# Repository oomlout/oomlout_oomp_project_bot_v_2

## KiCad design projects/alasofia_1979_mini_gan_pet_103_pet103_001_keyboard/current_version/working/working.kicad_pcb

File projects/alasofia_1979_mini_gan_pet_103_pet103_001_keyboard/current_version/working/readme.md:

# 1979_mini_gan_pet_103
 
## summary 
* id: alasofia_1979_mini_gan_pet_103_pet103_001_keyboard
* user: alasofia
* name: 1979_mini_gan_pet_103
* board: pet103_001_keyboard
* repo: https://github.com/Alasofia/1979-MINI-GAN-PET-103
* src_file_repo_kicad_pcb: KiCad/PET103_001_Keyboard/PET103_001_Keyboard.kicad_pcb
* src_file_repo_kicad_pcb_link: https://github.com/Alasofia/1979-MINI-GAN-PET-103/tree/main/KiCad/PET103_001_Keyboard/PET103_001_Keyboard.kicad_pcb

* src_file_repo_sch: KiCad/PET103_001_Keyboard/PET103_001_Keyboard.sch
* src_file_repo_sch_link: https://github.com/Alasofia/1979-MINI-GAN-PET-103/tree/main/KiCad/PET103_001_Keyboard/PET103_001_Keyboard.sch
* full details link: https://github.com/oomlout/oomlout_oomp_project_bot_v_2/tree/main/projects/alasofia_1979_mini_gan_pet_103_pet103_001_keyboard/current_version/working  

## schematic  
  
[schematic (pdf)](working_schematic.pdf) 

## pcb  

[board (pdf)](working.pdf)  

## working_bom
| Id | Designator | Footprint | Quantity | Designation | Supplier and ref |  | None | 
| --- | --- | --- | --- | --- | --- | --- | --- | 
| 1 | R1 | R_Axial_DIN0207_L6.3mm_D2.5mm_P10.16mm_Horizontal | 1 | 5K |  |  | [''] | 
| 2 | R2,R3 | R_Axial_DIN0207_L6.3mm_D2.5mm_P10.16mm_Horizontal | 2 | 4K6 |  |  | [''] | 
| 3 | R4,R5 | R_Axial_DIN0207_L6.3mm_D2.5mm_P10.16mm_Horizontal | 2 | 4K |  |  | [''] | 
| 4 | R6,R7 | R_Axial_DIN0207_L6.3mm_D2.5mm_P10.16mm_Horizontal | 2 | 3K5 |  |  | [''] | 
| 5 | R8,R9 | R_Axial_DIN0207_L6.3mm_D2.5mm_P10.16mm_Horizontal | 2 | 3K2 |  |  | [''] | 
| 6 | R10 | R_Axial_DIN0207_L6.3mm_D2.5mm_P10.16mm_Horizontal | 1 | 3K |  |  | [''] | 
| 7 | R11 | R_Axial_DIN0207_L6.3mm_D2.5mm_P10.16mm_Horizontal | 1 | 2K8 |  |  | [''] | 
| 8 | R12 | R_Axial_DIN0207_L6.3mm_D2.5mm_P10.16mm_Horizontal | 1 | 2K6 |  |  | [''] | 
| 9 | R13,R14 | R_Axial_DIN0207_L6.3mm_D2.5mm_P10.16mm_Horizontal | 2 | 2K5 |  |  | [''] | 
| 10 | R15 | R_Axial_DIN0207_L6.3mm_D2.5mm_P10.16mm_Horizontal | 1 | 2K3 |  |  | [''] | 
| 11 | R16,R17 | R_Axial_DIN0207_L6.3mm_D2.5mm_P10.16mm_Horizontal | 2 | 2K |  |  | [''] | 
| 12 | R18 | R_Axial_DIN0207_L6.3mm_D2.5mm_P10.16mm_Horizontal | 1 | 1K9 |  |  | [''] | 
| 13 | R19 | R_Axial_DIN0207_L6.3mm_D2.5mm_P10.16mm_Horizontal | 1 | 1K8 |  |  | [''] | 
| 14 | R20 | R_Axial_DIN0207_L6.3mm_D2.5mm_P10.16mm_Horizontal | 1 | 1K7 |  |  | [''] | 
| 15 | R21 | R_Axial_DIN0207_L6.3mm_D2.5mm_P10.16mm_Horizontal | 1 | 1K5 |  |  | [''] | 
| 16 | R22,R23 | R_Axial_DIN0207_L6.3mm_D2.5mm_P10.16mm_Horizontal | 2 | 1K4 |  |  | [''] | 
| 17 | R24 | R_Axial_DIN0207_L6.3mm_D2.5mm_P10.16mm_Horizontal | 1 | 1K3 |  |  | [''] | 
| 18 | R25 | R_Axial_DIN0207_L6.3mm_D2.5mm_P10.16mm_Horizontal | 1 | 22K |  |  | [''] | 

## bom_schematic
| Ref | Qnty | Value | Cmp name | Footprint | Description | Vendor | DNP | 
| --- | --- | --- | --- | --- | --- | --- | --- | 
| R1 | 1 | 5K | R_Small_US | Resistor_THT:R_Axial_DIN0207_L6.3mm_D2.5mm_P10.16mm_Horizontal | Resistor, small US symbol |  |  | 
| R2, R3 | 2 | 4K6 | R_Small_US | Resistor_THT:R_Axial_DIN0207_L6.3mm_D2.5mm_P10.16mm_Horizontal | Resistor, small US symbol |  |  | 
| R4, R5 | 2 | 4K | R_Small_US | Resistor_THT:R_Axial_DIN0207_L6.3mm_D2.5mm_P10.16mm_Horizontal | Resistor, small US symbol |  |  | 
| R6, R7 | 2 | 3K5 | R_Small_US | Resistor_THT:R_Axial_DIN0207_L6.3mm_D2.5mm_P10.16mm_Horizontal | Resistor, small US symbol |  |  | 
| R8, R9 | 2 | 3K2 | R_Small_US | Resistor_THT:R_Axial_DIN0207_L6.3mm_D2.5mm_P10.16mm_Horizontal | Resistor, small US symbol |  |  | 
| R10 | 1 | 3K | R_Small_US | Resistor_THT:R_Axial_DIN0207_L6.3mm_D2.5mm_P10.16mm_Horizontal | Resistor, small US symbol |  |  | 
| R11 | 1 | 2K8 | R_Small_US | Resistor_THT:R_Axial_DIN0207_L6.3mm_D2.5mm_P10.16mm_Horizontal | Resistor, small US symbol |  |  | 
| R12 | 1 | 2K6 | R_Small_US | Resistor_THT:R_Axial_DIN0207_L6.3mm_D2.5mm_P10.16mm_Horizontal | Resistor, small US symbol |  |  | 
| R13, R14 | 2 | 2K5 | R_Small_US | Resistor_THT:R_Axial_DIN0207_L6.3mm_D2.5mm_P10.16mm_Horizontal | Resistor, small US symbol |  |  | 
| R15 | 1 | 2K3 | R_Small_US | Resistor_THT:R_Axial_DIN0207_L6.3mm_D2.5mm_P10.16mm_Horizontal | Resistor, small US symbol |  |  | 
| R16, R17 | 2 | 2K | R_Small_US | Resistor_THT:R_Axial_DIN0207_L6.3mm_D2.5mm_P10.16mm_Horizontal | Resistor, small US symbol |  |  | 
| R18 | 1 | 1K9 | R_Small_US | Resistor_THT:R_Axial_DIN0207_L6.3mm_D2.5mm_P10.16mm_Horizontal | Resistor, small US symbol |  |  | 
| R19 | 1 | 1K8 | R_Small_US | Resistor_THT:R_Axial_DIN0207_L6.3mm_D2.5mm_P10.16mm_Horizontal | Resistor, small US symbol |  |  | 
| R20 | 1 | 1K7 | R_Small_US | Resistor_THT:R_Axial_DIN0207_L6.3mm_D2.5mm_P10.16mm_Horizontal | Resistor, small US symbol |  |  | 
| R21 | 1 | 1K5 | R_Small_US | Resistor_THT:R_Axial_DIN0207_L6.3mm_D2.5mm_P10.16mm_Horizontal | Resistor, small US symbol |  |  | 
| R22, R23 | 2 | 1K4 | R_Small_US | Resistor_THT:R_Axial_DIN0207_L6.3mm_D2.5mm_P10.16mm_Horizontal | Resistor, small US symbol |  |  | 
| R24 | 1 | 1K3 | R_Small_US | Resistor_THT:R_Axial_DIN0207_L6.3mm_D2.5mm_P10.16mm_Horizontal | Resistor, small US symbol |  |  | 
| R25 | 1 | 22K | R_Small_US | Resistor_THT:R_Axial_DIN0207_L6.3mm_D2.5mm_P10.16mm_Horizontal | Resistor, small US symbol |  |  | 
| SW1 | 1 | F_01 | SW_SPST | Connector_Wire:SolderWire-1.5sqmm_1x02_P7.8mm_D1.7mm_OD3.9mm | Single Pole Single Throw (SPST) switch |  |  | 
| SW2 | 1 | F#_01 | SW_SPST | Connector_Wire:SolderWire-1.5sqmm_1x02_P7.8mm_D1.7mm_OD3.9mm | Single Pole Single Throw (SPST) switch |  |  | 
| SW3 | 1 | G_01 | SW_SPST | Connector_Wire:SolderWire-1.5sqmm_1x02_P7.8mm_D1.7mm_OD3.9mm | Single Pole Single Throw (SPST) switch |  |  | 
| SW4 | 1 | G#_01 | SW_SPST | Connector_Wire:SolderWire-1.5sqmm_1x02_P7.8mm_D1.7mm_OD3.9mm | Single Pole Single Throw (SPST) switch |  |  | 
| SW5 | 1 | A_01 | SW_SPST | Connector_Wire:SolderWire-1.5sqmm_1x02_P7.8mm_D1.7mm_OD3.9mm | Single Pole Single Throw (SPST) switch |  |  | 
| SW6 | 1 | A#_01 | SW_SPST | Connector_Wire:SolderWire-1.5sqmm_1x02_P7.8mm_D1.7mm_OD3.9mm | Single Pole Single Throw (SPST) switch |  |  | 
| SW7 | 1 | B_01 | SW_SPST | Connector_Wire:SolderWire-1.5sqmm_1x02_P7.8mm_D1.7mm_OD3.9mm | Single Pole Single Throw (SPST) switch |  |  | 
| SW8 | 1 | C_01 | SW_SPST | Connector_Wire:SolderWire-1.5sqmm_1x02_P7.8mm_D1.7mm_OD3.9mm | Single Pole Single Throw (SPST) switch |  |  | 
| SW9 | 1 | C#_01 | SW_SPST | Connector_Wire:SolderWire-1.5sqmm_1x02_P7.8mm_D1.7mm_OD3.9mm | Single Pole Single Throw (SPST) switch |  |  | 
| SW10 | 1 | D_01 | SW_SPST | Connector_Wire:SolderWire-1.5sqmm_1x02_P7.8mm_D1.7mm_OD3.9mm | Single Pole Single Throw (SPST) switch |  |  | 
| SW11 | 1 | D#_01 | SW_SPST | Connector_Wire:SolderWire-1.5sqmm_1x02_P7.8mm_D1.7mm_OD3.9mm | Single Pole Single Throw (SPST) switch |  |  | 
| SW12 | 1 | E_01 | SW_SPST | Connector_Wire:SolderWire-1.5sqmm_1x02_P7.8mm_D1.7mm_OD3.9mm | Single Pole Single Throw (SPST) switch |  |  | 
| SW13 | 1 | F_02 | SW_SPST | Connector_Wire:SolderWire-1.5sqmm_1x02_P7.8mm_D1.7mm_OD3.9mm | Single Pole Single Throw (SPST) switch |  |  | 
| SW14 | 1 | F#_02 | SW_SPST | Connector_Wire:SolderWire-1.5sqmm_1x02_P7.8mm_D1.7mm_OD3.9mm | Single Pole Single Throw (SPST) switch |  |  | 
| SW15 | 1 | G_02 | SW_SPST | Connector_Wire:SolderWire-1.5sqmm_1x02_P7.8mm_D1.7mm_OD3.9mm | Single Pole Single Throw (SPST) switch |  |  | 
| SW16 | 1 | G#_02 | SW_SPST | Connector_Wire:SolderWire-1.5sqmm_1x02_P7.8mm_D1.7mm_OD3.9mm | Single Pole Single Throw (SPST) switch |  |  | 
| SW17 | 1 | A_02 | SW_SPST | Connector_Wire:SolderWire-1.5sqmm_1x02_P7.8mm_D1.7mm_OD3.9mm | Single Pole Single Throw (SPST) switch |  |  | 
| SW18 | 1 | A#_02 | SW_SPST | Connector_Wire:SolderWire-1.5sqmm_1x02_P7.8mm_D1.7mm_OD3.9mm | Single Pole Single Throw (SPST) switch |  |  | 
| SW19 | 1 | B_02 | SW_SPST | Connector_Wire:SolderWire-1.5sqmm_1x02_P7.8mm_D1.7mm_OD3.9mm | Single Pole Single Throw (SPST) switch |  |  | 
| SW20 | 1 | C_02 | SW_SPST | Connector_Wire:SolderWire-1.5sqmm_1x02_P7.8mm_D1.7mm_OD3.9mm | Single Pole Single Throw (SPST) switch |  |  | 
| SW21 | 1 | C#_02 | SW_SPST | Connector_Wire:SolderWire-1.5sqmm_1x02_P7.8mm_D1.7mm_OD3.9mm | Single Pole Single Throw (SPST) switch |  |  | 
| SW22 | 1 | D_02 | SW_SPST | Connector_Wire:SolderWire-1.5sqmm_1x02_P7.8mm_D1.7mm_OD3.9mm | Single Pole Single Throw (SPST) switch |  |  | 
| SW23 | 1 | D#_02 | SW_SPST | Connector_Wire:SolderWire-1.5sqmm_1x02_P7.8mm_D1.7mm_OD3.9mm | Single Pole Single Throw (SPST) switch |  |  | 
| SW24 | 1 | E_02 | SW_SPST | Connector_Wire:SolderWire-1.5sqmm_1x02_P7.8mm_D1.7mm_OD3.9mm | Single Pole Single Throw (SPST) switch |  |  | 
| SW25 | 1 | F_03 | SW_SPST | Connector_Wire:SolderWire-1.5sqmm_1x02_P7.8mm_D1.7mm_OD3.9mm | Single Pole Single Throw (SPST) switch |  |  |

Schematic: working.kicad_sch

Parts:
J1: Keyboard 1; SolderWire-0.15sqmm_1x01_D0.5mm_OD1.5mm
J2: Keyboard 2; SolderWire-0.15sqmm_1x01_D0.5mm_OD1.5mm
R1: 5K; R_Axial_DIN0207_L6.3mm_D2.5mm_P10.16mm_Horizontal
R2, R3: 4K6; R_Axial_DIN0207_L6.3mm_D2.5mm_P10.16mm_Horizontal
R4, R5: 4K; R_Axial_DIN0207_L6.3mm_D2.5mm_P10.16mm_Horizontal
R6, R7: 3K5; R_Axial_DIN0207_L6.3mm_D2.5mm_P10.16mm_Horizontal
R8, R9: 3K2; R_Axial_DIN0207_L6.3mm_D2.5mm_P10.16mm_Horizontal
R10: 3K; R_Axial_DIN0207_L6.3mm_D2.5mm_P10.16mm_Horizontal
R11: 2K8; R_Axial_DIN0207_L6.3mm_D2.5mm_P10.16mm_Horizontal
R12: 2K6; R_Axial_DIN0207_L6.3mm_D2.5mm_P10.16mm_Horizontal
R13, R14: 2K5; R_Axial_DIN0207_L6.3mm_D2.5mm_P10.16mm_Horizontal
R15: 2K3; R_Axial_DIN0207_L6.3mm_D2.5mm_P10.16mm_Horizontal
R16, R17: 2K; R_Axial_DIN0207_L6.3mm_D2.5mm_P10.16mm_Horizontal
R18: 1K9; R_Axial_DIN0207_L6.3mm_D2.5mm_P10.16mm_Horizontal
R19: 1K8; R_Axial_DIN0207_L6.3mm_D2.5mm_P10.16mm_Horizontal
R20: 1K7; R_Axial_DIN0207_L6.3mm_D2.5mm_P10.16mm_Horizontal
R21: 1K5; R_Axial_DIN0207_L6.3mm_D2.5mm_P10.16mm_Horizontal
R22, R23: 1K4; R_Axial_DIN0207_L6.3mm_D2.5mm_P10.16mm_Horizontal
R24: 1K3; R_Axial_DIN0207_L6.3mm_D2.5mm_P10.16mm_Horizontal
R25: 22K; R_Axial_DIN0207_L6.3mm_D2.5mm_P10.16mm_Horizontal
SW1: F_01; SolderWire-1.5sqmm_1x02_P7.8mm_D1.7mm_OD3.9mm
SW2: F#_01; SolderWire-1.5sqmm_1x02_P7.8mm_D1.7mm_OD3.9mm
SW3: G_01; SolderWire-1.5sqmm_1x02_P7.8mm_D1.7mm_OD3.9mm
SW4: G#_01; SolderWire-1.5sqmm_1x02_P7.8mm_D1.7mm_OD3.9mm
SW5: A_01; SolderWire-1.5sqmm_1x02_P7.8mm_D1.7mm_OD3.9mm
SW6: A#_01; SolderWire-1.5sqmm_1x02_P7.8mm_D1.7mm_OD3.9mm
SW7: B_01; SolderWire-1.5sqmm_1x02_P7.8mm_D1.7mm_OD3.9mm
SW8: C_01; SolderWire-1.5sqmm_1x02_P7.8mm_D1.7mm_OD3.9mm
SW9: C#_01; SolderWire-1.5sqmm_1x02_P7.8mm_D1.7mm_OD3.9mm
SW10: D_01; SolderWire-1.5sqmm_1x02_P7.8mm_D1.7mm_OD3.9mm
SW11: D#_01; SolderWire-1.5sqmm_1x02_P7.8mm_D1.7mm_OD3.9mm
SW12: E_01; SolderWire-1.5sqmm_1x02_P7.8mm_D1.7mm_OD3.9mm
SW13: F_02; SolderWire-1.5sqmm_1x02_P7.8mm_D1.7mm_OD3.9mm
SW14: F#_02; SolderWire-1.5sqmm_1x02_P7.8mm_D1.7mm_OD3.9mm
SW15: G_02; SolderWire-1.5sqmm_1x02_P7.8mm_D1.7mm_OD3.9mm
SW16: G#_02; SolderWire-1.5sqmm_1x02_P7.8mm_D1.7mm_OD3.9mm
SW17: A_02; SolderWire-1.5sqmm_1x02_P7.8mm_D1.7mm_OD3.9mm
SW18: A#_02; SolderWire-1.5sqmm_1x02_P7.8mm_D1.7mm_OD3.9mm
SW19: B_02; SolderWire-1.5sqmm_1x02_P7.8mm_D1.7mm_OD3.9mm
SW20: C_02; SolderWire-1.5sqmm_1x02_P7.8mm_D1.7mm_OD3.9mm
SW21: C#_02; SolderWire-1.5sqmm_1x02_P7.8mm_D1.7mm_OD3.9mm
SW22: D_02; SolderWire-1.5sqmm_1x02_P7.8mm_D1.7mm_OD3.9mm
SW23: D#_02; SolderWire-1.5sqmm_1x02_P7.8mm_D1.7mm_OD3.9mm
SW24: E_02; SolderWire-1.5sqmm_1x02_P7.8mm_D1.7mm_OD3.9mm
SW25: F_03; SolderWire-1.5sqmm_1x02_P7.8mm_D1.7mm_OD3.9mm

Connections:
unnamed: R1.1, SW1.1 (A)
unnamed: R1.2, R2.1, SW2.1 (A)
unnamed: R2.2, R3.1, SW3.1 (A)
unnamed: R3.2, R4.1, SW4.1 (A)
unnamed: R4.2, R5.1, SW5.1 (A)
unnamed: R5.2, R6.1, SW6.1 (A)
unnamed: R6.2, R7.1, SW7.1 (A)
unnamed: R7.2, R8.1, SW8.1 (A)
unnamed: R8.2, R9.1, SW9.1 (A)
unnamed: R9.2, R10.1, SW10.1 (A)
unnamed: R10.2, R11.1, SW11.1 (A)
unnamed: R11.2, R12.1, SW12.1 (A)
unnamed: R12.2, R13.1, SW13.1 (A)
unnamed: R13.2, R14.1, SW14.1 (A)
unnamed: R14.2, R15.1, SW15.1 (A)
unnamed: R15.2, R16.1, SW16.1 (A)
unnamed: R16.2, R17.1, SW17.1 (A)
unnamed: R17.2, R18.1, SW18.1 (A)
unnamed: R18.2, R19.1, SW19.1 (A)
unnamed: R19.2, R20.1, SW20.1 (A)
unnamed: R20.2, R21.1, SW21.1 (A)
unnamed: R21.2, R22.1, SW22.1 (A)
unnamed: R22.2, R23.1, SW23.1 (A)
unnamed: R23.2, R24.1, SW24.1 (A)
unnamed: R24.2, R25.1, SW25.1 (A)
P: J2.1, SW1.2 (B), SW2.2 (B), SW3.2 (B), SW4.2 (B), SW5.2 (B), SW6.2 (B), SW7.2 (B), SW8.2 (B), SW9.2 (B), SW10.2 (B), SW11.2 (B), SW12.2 (B), SW13.2 (B), SW14.2 (B), SW15.2 (B), SW16.2 (B), SW17.2 (B), SW18.2 (B), SW19.2 (B), SW20.2 (B), SW21.2 (B), SW22.2 (B), SW23.2 (B), SW24.2 (B), SW25.2 (B)
Y: J1.1, R25.2

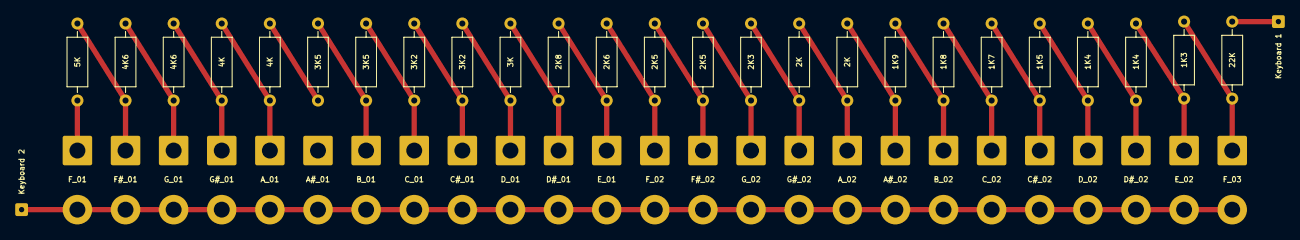
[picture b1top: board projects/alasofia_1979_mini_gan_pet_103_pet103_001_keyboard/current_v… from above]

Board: 2 copper layers, 52 parts (0 on the bottom side), 27 nets.

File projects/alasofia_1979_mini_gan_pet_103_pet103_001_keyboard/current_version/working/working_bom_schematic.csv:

"Source:","C:\gh\oomlout_oomp_project_bot_v_2\projects\alasofia_1979_mini_gan_pet_103_pet103_001_keyboard\current_version\working\working.kicad_sch"
"Date:","18/09/2023 18:38:11"
"Tool:","Eeschema 7.0.6"
"Generator:","C:/Program Files/KiCad/7.0/bin/scripting/plugins/bom_csv_grouped_by_value_with_fp.py"
"Component Count:","50"
"Ref","Qnty","Value","Cmp name","Footprint","Description","Vendor","DNP"
"R1","1","5K","R_Small_US","Resistor_THT:R_Axial_DIN0207_L6.3mm_D2.5mm_P10.16mm_Horizontal","Resistor, small US symbol","",""
"R2, R3","2","4K6","R_Small_US","Resistor_THT:R_Axial_DIN0207_L6.3mm_D2.5mm_P10.16mm_Horizontal","Resistor, small US symbol","",""
"R4, R5","2","4K","R_Small_US","Resistor_THT:R_Axial_DIN0207_L6.3mm_D2.5mm_P10.16mm_Horizontal","Resistor, small US symbol","",""
"R6, R7","2","3K5","R_Small_US","Resistor_THT:R_Axial_DIN0207_L6.3mm_D2.5mm_P10.16mm_Horizontal","Resistor, small US symbol","",""
"R8, R9","2","3K2","R_Small_US","Resistor_THT:R_Axial_DIN0207_L6.3mm_D2.5mm_P10.16mm_Horizontal","Resistor, small US symbol","",""
"R10","1","3K","R_Small_US","Resistor_THT:R_Axial_DIN0207_L6.3mm_D2.5mm_P10.16mm_Horizontal","Resistor, small US symbol","",""
"R11","1","2K8","R_Small_US","Resistor_THT:R_Axial_DIN0207_L6.3mm_D2.5mm_P10.16mm_Horizontal","Resistor, small US symbol","",""
"R12","1","2K6","R_Small_US","Resistor_THT:R_Axial_DIN0207_L6.3mm_D2.5mm_P10.16mm_Horizontal","Resistor, small US symbol","",""
"R13, R14","2","2K5","R_Small_US","Resistor_THT:R_Axial_DIN0207_L6.3mm_D2.5mm_P10.16mm_Horizontal","Resistor, small US symbol","",""
"R15","1","2K3","R_Small_US","Resistor_THT:R_Axial_DIN0207_L6.3mm_D2.5mm_P10.16mm_Horizontal","Resistor, small US symbol","",""
"R16, R17","2","2K","R_Small_US","Resistor_THT:R_Axial_DIN0207_L6.3mm_D2.5mm_P10.16mm_Horizontal","Resistor, small US symbol","",""
"R18","1","1K9","R_Small_US","Resistor_THT:R_Axial_DIN0207_L6.3mm_D2.5mm_P10.16mm_Horizontal","Resistor, small US symbol","",""
"R19","1","1K8","R_Small_US","Resistor_THT:R_Axial_DIN0207_L6.3mm_D2.5mm_P10.16mm_Horizontal","Resistor, small US symbol","",""
"R20","1","1K7","R_Small_US","Resistor_THT:R_Axial_DIN0207_L6.3mm_D2.5mm_P10.16mm_Horizontal","Resistor, small US symbol","",""
"R21","1","1K5","R_Small_US","Resistor_THT:R_Axial_DIN0207_L6.3mm_D2.5mm_P10.16mm_Horizontal","Resistor, small US symbol","",""
"R22, R23","2","1K4","R_Small_US","Resistor_THT:R_Axial_DIN0207_L6.3mm_D2.5mm_P10.16mm_Horizontal","Resistor, small US symbol","",""
"R24","1","1K3","R_Small_US","Resistor_THT:R_Axial_DIN0207_L6.3mm_D2.5mm_P10.16mm_Horizontal","Resistor, small US symbol","",""
"R25","1","22K","R_Small_US","Resistor_THT:R_Axial_DIN0207_L6.3mm_D2.5mm_P10.16mm_Horizontal","Resistor, small US symbol","",""
"SW1","1","F_01","SW_SPST","Connector_Wire:SolderWire-1.5sqmm_1x02_P7.8mm_D1.7mm_OD3.9mm","Single Pole Single Throw (SPST) switch","",""
"SW2","1","F#_01","SW_SPST","Connector_Wire:SolderWire-1.5sqmm_1x02_P7.8mm_D1.7mm_OD3.9mm","Single Pole Single Throw (SPST) switch","",""
"SW3","1","G_01","SW_SPST","Connector_Wire:SolderWire-1.5sqmm_1x02_P7.8mm_D1.7mm_OD3.9mm","Single Pole Single Throw (SPST) switch","",""
"SW4","1","G#_01","SW_SPST","Connector_Wire:SolderWire-1.5sqmm_1x02_P7.8mm_D1.7mm_OD3.9mm","Single Pole Single Throw (SPST) switch","",""
"SW5","1","A_01","SW_SPST","Connector_Wire:SolderWire-1.5sqmm_1x02_P7.8mm_D1.7mm_OD3.9mm","Single Pole Single Throw (SPST) switch","",""
"SW6","1","A#_01","SW_SPST","Connector_Wire:SolderWire-1.5sqmm_1x02_P7.8mm_D1.7mm_OD3.9mm","Single Pole Single Throw (SPST) switch","",""
"SW7","1","B_01","SW_SPST","Connector_Wire:SolderWire-1.5sqmm_1x02_P7.8mm_D1.7mm_OD3.9mm","Single Pole Single Throw (SPST) switch","",""
"SW8","1","C_01","SW_SPST","Connector_Wire:SolderWire-1.5sqmm_1x02_P7.8mm_D1.7mm_OD3.9mm","Single Pole Single Throw (SPST) switch","",""
"SW9","1","C#_01","SW_SPST","Connector_Wire:SolderWire-1.5sqmm_1x02_P7.8mm_D1.7mm_OD3.9mm","Single Pole Single Throw (SPST) switch","",""
"SW10","1","D_01","SW_SPST","Connector_Wire:SolderWire-1.5sqmm_1x02_P7.8mm_D1.7mm_OD3.9mm","Single Pole Single Throw (SPST) switch","",""
"SW11","1","D#_01","SW_SPST","Connector_Wire:SolderWire-1.5sqmm_1x02_P7.8mm_D1.7mm_OD3.9mm","Single Pole Single Throw (SPST) switch","",""
"SW12","1","E_01","SW_SPST","Connector_Wire:SolderWire-1.5sqmm_1x02_P7.8mm_D1.7mm_OD3.9mm","Single Pole Single Throw (SPST) switch","",""
"SW13","1","F_02","SW_SPST","Connector_Wire:SolderWire-1.5sqmm_1x02_P7.8mm_D1.7mm_OD3.9mm","Single Pole Single Throw (SPST) switch","",""
"SW14","1","F#_02","SW_SPST","Connector_Wire:SolderWire-1.5sqmm_1x02_P7.8mm_D1.7mm_OD3.9mm","Single Pole Single Throw (SPST) switch","",""
"SW15","1","G_02","SW_SPST","Connector_Wire:SolderWire-1.5sqmm_1x02_P7.8mm_D1.7mm_OD3.9mm","Single Pole Single Throw (SPST) switch","",""
"SW16","1","G#_02","SW_SPST","Connector_Wire:SolderWire-1.5sqmm_1x02_P7.8mm_D1.7mm_OD3.9mm","Single Pole Single Throw (SPST) switch","",""
"SW17","1","A_02","SW_SPST","Connector_Wire:SolderWire-1.5sqmm_1x02_P7.8mm_D1.7mm_OD3.9mm","Single Pole Single Throw (SPST) switch","",""
"SW18","1","A#_02","SW_SPST","Connector_Wire:SolderWire-1.5sqmm_1x02_P7.8mm_D1.7mm_OD3.9mm","Single Pole Single Throw (SPST) switch","",""
"SW19","1","B_02","SW_SPST","Connector_Wire:SolderWire-1.5sqmm_1x02_P7.8mm_D1.7mm_OD3.9mm","Single Pole Single Throw (SPST) switch","",""
"SW20","1","C_02","SW_SPST","Connector_Wire:SolderWire-1.5sqmm_1x02_P7.8mm_D1.7mm_OD3.9mm","Single Pole Single Throw (SPST) switch","",""
"SW21","1","C#_02","SW_SPST","Connector_Wire:SolderWire-1.5sqmm_1x02_P7.8mm_D1.7mm_OD3.9mm","Single Pole Single Throw (SPST) switch","",""
"SW22","1","D_02","SW_SPST","Connector_Wire:SolderWire-1.5sqmm_1x02_P7.8mm_D1.7mm_OD3.9mm","Single Pole Single Throw (SPST) switch","",""
"SW23","1","D#_02","SW_SPST","Connector_Wire:SolderWire-1.5sqmm_1x02_P7.8mm_D1.7mm_OD3.9mm","Single Pole Single Throw (SPST) switch","",""
"SW24","1","E_02","SW_SPST","Connector_Wire:SolderWire-1.5sqmm_1x02_P7.8mm_D1.7mm_OD3.9mm","Single Pole Single Throw (SPST) switch","",""
"SW25","1","F_03","SW_SPST","Connector_Wire:SolderWire-1.5sqmm_1x02_P7.8mm_D1.7mm_OD3.9mm","Single Pole Single Throw (SPST) switch","",""

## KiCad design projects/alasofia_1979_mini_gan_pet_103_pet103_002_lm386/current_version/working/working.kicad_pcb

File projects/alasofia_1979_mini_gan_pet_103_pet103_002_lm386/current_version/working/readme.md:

# 1979_mini_gan_pet_103
 
## summary 
* id: alasofia_1979_mini_gan_pet_103_pet103_002_lm386
* user: alasofia
* name: 1979_mini_gan_pet_103
* board: pet103_002_lm386
* repo: https://github.com/Alasofia/1979-MINI-GAN-PET-103
* src_file_repo_kicad_pcb: KiCad/PET103_002_LM386/PET103_002_LM386.kicad_pcb
* src_file_repo_kicad_pcb_link: https://github.com/Alasofia/1979-MINI-GAN-PET-103/tree/main/KiCad/PET103_002_LM386/PET103_002_LM386.kicad_pcb

* src_file_repo_sch: KiCad/PET103_002_LM386/PET103_002_LM386.sch
* src_file_repo_sch_link: https://github.com/Alasofia/1979-MINI-GAN-PET-103/tree/main/KiCad/PET103_002_LM386/PET103_002_LM386.sch
* full details link: https://github.com/oomlout/oomlout_oomp_project_bot_v_2/tree/main/projects/alasofia_1979_mini_gan_pet_103_pet103_002_lm386/current_version/working  

## schematic  
  
[schematic (pdf)](working_schematic.pdf) 

## pcb  

[board (pdf)](working.pdf)  

## working_bom
| Id | Designator | Footprint | Quantity | Designation | Supplier and ref |  | None | 
| --- | --- | --- | --- | --- | --- | --- | --- | 
| 1 | C2,C8 | CP_Radial_D5.0mm_P2.50mm | 2 | 470ÂµF |  |  | [''] | 
| 2 | C10 | CP_Radial_D5.0mm_P2.50mm | 1 | 100ÂµF |  |  | [''] | 
| 3 | C11,C13,C15,C16,C17 | CP_Radial_D5.0mm_P2.50mm | 5 | 1ÂµF |  |  | [''] | 
| 4 | C12 | C_Disc_D4.7mm_W2.5mm_P5.00mm | 1 | 223 |  |  | [''] | 
| 5 | C14 | C_Disc_D4.7mm_W2.5mm_P5.00mm | 1 | 333 |  |  | [''] | 
| 6 | Q1 | TO-92_Inline | 1 | 2SC1815 |  |  | [''] | 
| 7 | R2,R1 | R_Axial_DIN0207_L6.3mm_D2.5mm_P10.16mm_Horizontal | 2 | 100Î© |  |  | [''] | 
| 8 | R3,R7,R10 | R_Axial_DIN0207_L6.3mm_D2.5mm_P10.16mm_Horizontal | 3 | 4.7K |  |  | [''] | 
| 9 | R4 | R_Axial_DIN0207_L6.3mm_D2.5mm_P10.16mm_Horizontal | 1 | 1M |  |  | [''] | 
| 10 | R5 | R_Axial_DIN0207_L6.3mm_D2.5mm_P10.16mm_Horizontal | 1 | 100K |  |  | [''] | 
| 11 | R6,R8 | R_Axial_DIN0207_L6.3mm_D2.5mm_P10.16mm_Horizontal | 2 | 1K |  |  | [''] | 
| 12 | R9,R11 | R_Axial_DIN0207_L6.3mm_D2.5mm_P10.16mm_Horizontal | 2 | 10K |  |  | [''] | 
| 13 | R12 | R_Axial_DIN0207_L6.3mm_D2.5mm_P10.16mm_Horizontal | 1 | 18K |  |  | [''] | 
| 14 | R13 | Potentiometer_Bourns_3266W_Vertical | 1 | 5K |  |  | [''] | 
| 15 | U1 | DIP-8_W7.62mm_LongPads | 1 | LA6458 |  |  | [''] | 
| 16 | C1,C5 | C_Disc_D4.7mm_W2.5mm_P5.00mm | 2 | 0.27ÂµF |  |  | [''] | 
| 17 | C3 | C_Disc_D4.7mm_W2.5mm_P5.00mm | 1 | 47pF |  |  | [''] | 
| 18 | C6,C7 | CP_Radial_D5.0mm_P2.50mm | 2 | 10ÂµF |  |  | [''] | 
| 19 | U2 | DIP-8_W7.62mm_LongPads | 1 | LM386 |  |  | [''] | 

## bom_schematic
no data

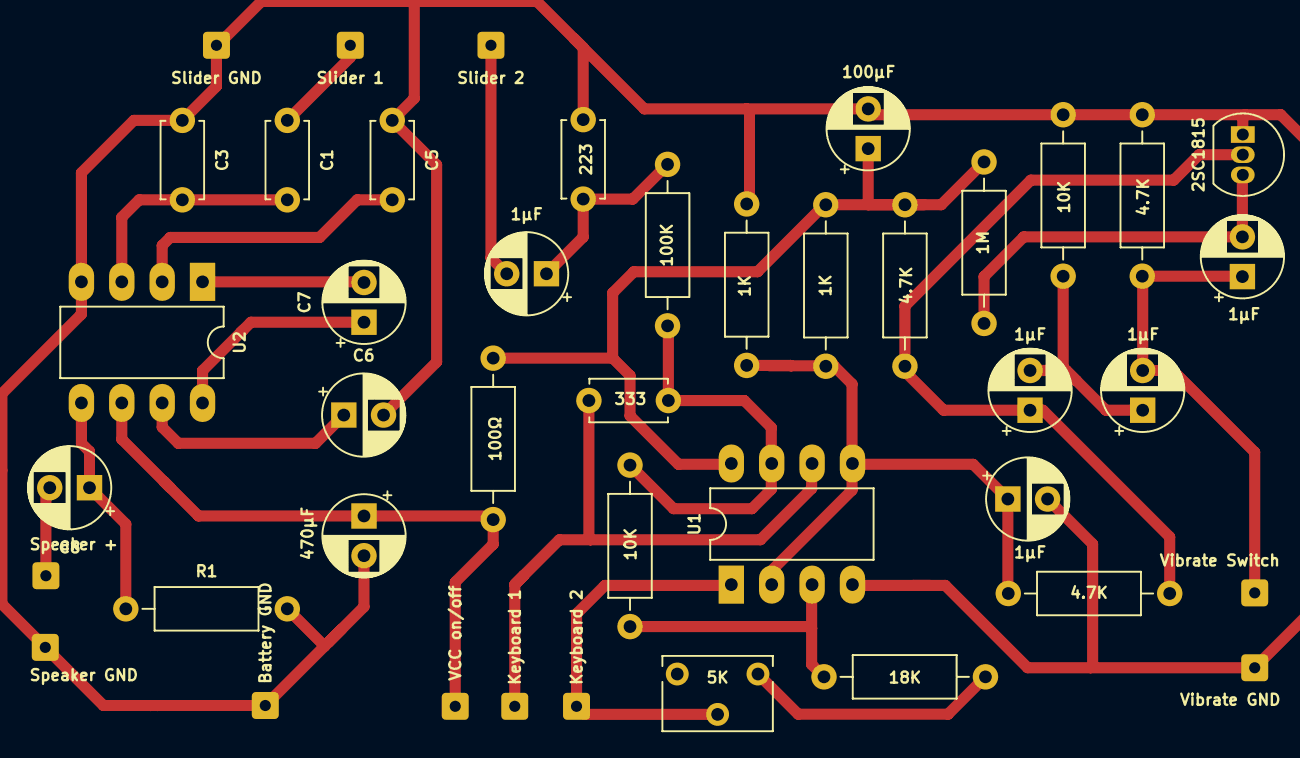
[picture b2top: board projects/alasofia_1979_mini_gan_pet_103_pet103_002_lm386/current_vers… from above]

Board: 2 copper layers, 42 parts (0 on the bottom side), 23 nets.

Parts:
C1, C5: 0.27µF; C_Disc_D4.7mm_W2.5mm_P5.00mm
C2, C8: 470µF; CP_Radial_D5.0mm_P2.50mm
C3: 47pF; C_Disc_D4.7mm_W2.5mm_P5.00mm
C6, C7: 10µF; CP_Radial_D5.0mm_P2.50mm
C10: 100µF; CP_Radial_D5.0mm_P2.50mm
C11, C13, C15, C16, C17: 1µF; CP_Radial_D5.0mm_P2.50mm
C12: 223; C_Disc_D4.7mm_W2.5mm_P5.00mm
C14: 333; C_Disc_D4.7mm_W2.5mm_P5.00mm
J1: Battery GND; SolderWire-0.15sqmm_1x01_D0.5mm_OD1.5mm
J2: Speaker GND; SolderWire-0.15sqmm_1x01_D0.5mm_OD1.5mm
J3: Slider GND; SolderWire-0.15sqmm_1x01_D0.5mm_OD1.5mm
J4: Vibrate GND; SolderWire-0.15sqmm_1x01_D0.5mm_OD1.5mm
J5: VCC on/off; SolderWire-0.15sqmm_1x01_D0.5mm_OD1.5mm
J6: Speaker +; SolderWire-0.15sqmm_1x01_D0.5mm_OD1.5mm
J7: Slider 1; SolderWire-0.15sqmm_1x01_D0.5mm_OD1.5mm
J8: Slider 2; SolderWire-0.15sqmm_1x01_D0.5mm_OD1.5mm
J9: Keyboard 1; SolderWire-0.15sqmm_1x01_D0.5mm_OD1.5mm
J10: Keyboard 2; SolderWire-0.15sqmm_1x01_D0.5mm_OD1.5mm
J11: Vibrate Switch; SolderWire-0.15sqmm_1x01_D0.5mm_OD1.5mm
Q1: 2SC1815; TO-92_Inline
R1, R2: 100Ω; R_Axial_DIN0207_L6.3mm_D2.5mm_P10.16mm_Horizontal
R3, R7, R10: 4.7K; R_Axial_DIN0207_L6.3mm_D2.5mm_P10.16mm_Horizontal
R4: 1M; R_Axial_DIN0207_L6.3mm_D2.5mm_P10.16mm_Horizontal
R5: 100K; R_Axial_DIN0207_L6.3mm_D2.5mm_P10.16mm_Horizontal
R6, R8: 1K; R_Axial_DIN0207_L6.3mm_D2.5mm_P10.16mm_Horizontal
R9, R11: 10K; R_Axial_DIN0207_L6.3mm_D2.5mm_P10.16mm_Horizontal
R12: 18K; R_Axial_DIN0207_L6.3mm_D2.5mm_P10.16mm_Horizontal
R13: 5K; Potentiometer_Bourns_3266W_Vertical
U1: LA6458; DIP-8_W7.62mm_LongPads
U2: LM386; DIP-8_W7.62mm_LongPads

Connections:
G: C11.2, J8.1
GND: C2.2, C3.1, C5.1, C6.2, C10.2, C12.2, C16.2, J1.1, J2.1, J3.1, J4.1, Q1.1, R1.2, R7.2, R8.1, R9.2, U1.4, U2.4
unnamed: C1.2, C3.2, U2.3
unnamed: C5.2, U2.2
unnamed: C6.1, U2.7
unnamed: C7.1, U2.8
unnamed: C7.2, U2.1
unnamed: C8.1, R1.1, U2.5
unnamed: C10.1, R2.1, R3.2, R4.2, R6.2, U1.8
unnamed: C11.1, C12.1, R5.1
unnamed: C13.2, Q1.3, R4.1
unnamed: C14.1, R5.2, R11.2, U1.7
unnamed: C15.1, C17.2, R9.1
unnamed: C16.1, R6.1, R8.2, R10.2, U1.2, U1.5
unnamed: C17.1, Q1.2, R3.1, R10.1
unnamed: R11.1, R12.2, U1.3
unnamed: R12.1, R13.1
O: C1.1, J7.1
P: J10.1, R13.2, U1.1
V: C13.1, C15.2, J11.1, R7.1
VCC: C2.1, J5.1, R2.2, U2.6
W: C8.2, J6.1
Y: C14.2, J9.1, U1.6

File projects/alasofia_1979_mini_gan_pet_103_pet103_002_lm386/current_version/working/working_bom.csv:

"Id";"Designator";"Footprint";"Quantity";"Designation";"Supplier and ref";
1;"C2,C8";"CP_Radial_D5.0mm_P2.50mm";2;"470µF";;;
2;"C10";"CP_Radial_D5.0mm_P2.50mm";1;"100µF";;;
3;"C11,C13,C15,C16,C17";"CP_Radial_D5.0mm_P2.50mm";5;"1µF";;;
4;"C12";"C_Disc_D4.7mm_W2.5mm_P5.00mm";1;"223";;;
5;"C14";"C_Disc_D4.7mm_W2.5mm_P5.00mm";1;"333";;;
6;"Q1";"TO-92_Inline";1;"2SC1815";;;
7;"R2,R1";"R_Axial_DIN0207_L6.3mm_D2.5mm_P10.16mm_Horizontal";2;"100Ω";;;
8;"R3,R7,R10";"R_Axial_DIN0207_L6.3mm_D2.5mm_P10.16mm_Horizontal";3;"4.7K";;;
9;"R4";"R_Axial_DIN0207_L6.3mm_D2.5mm_P10.16mm_Horizontal";1;"1M";;;
10;"R5";"R_Axial_DIN0207_L6.3mm_D2.5mm_P10.16mm_Horizontal";1;"100K";;;
11;"R6,R8";"R_Axial_DIN0207_L6.3mm_D2.5mm_P10.16mm_Horizontal";2;"1K";;;
12;"R9,R11";"R_Axial_DIN0207_L6.3mm_D2.5mm_P10.16mm_Horizontal";2;"10K";;;
13;"R12";"R_Axial_DIN0207_L6.3mm_D2.5mm_P10.16mm_Horizontal";1;"18K";;;
14;"R13";"Potentiometer_Bourns_3266W_Vertical";1;"5K";;;
15;"U1";"DIP-8_W7.62mm_LongPads";1;"LA6458";;;
16;"C1,C5";"C_Disc_D4.7mm_W2.5mm_P5.00mm";2;"0.27µF";;;
17;"C3";"C_Disc_D4.7mm_W2.5mm_P5.00mm";1;"47pF";;;
18;"C6,C7";"CP_Radial_D5.0mm_P2.50mm";2;"10µF";;;
19;"U2";"DIP-8_W7.62mm_LongPads";1;"LM386";;;

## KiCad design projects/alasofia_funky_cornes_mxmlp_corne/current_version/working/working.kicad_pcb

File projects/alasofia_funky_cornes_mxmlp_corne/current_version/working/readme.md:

# funky_cornes
 
## summary 
* id: alasofia_funky_cornes_mxmlp_corne
* user: alasofia
* name: funky_cornes
* board: mxmlp_corne
* repo: https://github.com/Alasofia/Funky-Cornes
* src_file_repo_kicad_pcb: MXMLP/MXMLP-Corne.kicad_pcb
* src_file_repo_kicad_pcb_link: https://github.com/Alasofia/Funky-Cornes/tree/master/MXMLP/MXMLP-Corne.kicad_pcb

* src_file_repo_sch: MXMLP/MXMLP-Corne.sch
* src_file_repo_sch_link: https://github.com/Alasofia/Funky-Cornes/tree/master/MXMLP/MXMLP-Corne.sch
* full details link: https://github.com/oomlout/oomlout_oomp_project_bot_v_2/tree/main/projects/alasofia_funky_cornes_mxmlp_corne/current_version/working  

## schematic  
  
[schematic (pdf)](working_schematic.pdf) 

## pcb  

[board (pdf)](working.pdf)  

## working_bom
| Id | Designator | Footprint | Quantity | Designation | Supplier and ref |  | None | 
| --- | --- | --- | --- | --- | --- | --- | --- | 
| 1 | D1,D2,D3,D4,D5,D7,D8,D9,D10,D11,D12,D13,D14,D15,D16,D17,D18,D19,D20,D21,D23,D24,D25,D27,D29,D30,D31,D32,D33,D34,D35,D36,D37,D38,D39,D40,D41,D42,D22,D6,D28,D26 | Diode-Hybrid-Back | 42 | D |  |  | [''] | 
| 2 | SW2,SW3,SW4,SW5,SW7,SW8,SW9,SW10,SW11,SW12,SW13,SW14,SW15,SW16,SW17,SW18,SW19,SW20,SW21,SW42,SW37,SW38,SW39,SW40,SW41,SW25,SW26,SW28,SW24,SW29,SW35,SW36,SW22,SW23,SW30,SW31,SW32,SW33,SW34,SW1,SW6,SW27 | MXMountLP-1U | 42 | SW_Push |  |  | [''] | 
| 3 | U4,U4,U4,U4,U4,U4,U4,U4,U4,U4 | MountingHole | 10 | HOLE |  |  | [''] | 
| 4 | J1,J2 | TRRS-PJ-320A | 2 | Conn_01x04_Female |  |  | [''] | 
| 5 | REF**,REF**,REF**,REF**,REF**,REF**,REF**,REF** | breakaway-mousebites | 8 | breakaway-mousebites |  |  | [''] | 
| 6 | U1,U2 | ProMicro | 2 | ProMicro |  |  | [''] | 

## bom_schematic
| Ref | Qnty | Value | Cmp name | Footprint | Description | Vendor | DNP | 
| --- | --- | --- | --- | --- | --- | --- | --- | 
| D1, D2, D3, D4, D5, D6, D7, D8, D9, D10, D11, D12, D13, D14, D15, D16, D17, D18, D19, D20, D21, D22, D23, D24, D25, D26, D27, D28, D29, D30, D31, D32, D33, D34, D35, D36, D37, D38, D39, D40, D41, D42 | 42 | D | D | Keebio-Parts:Diode-Hybrid-Back | Diode |  |  | 
| J1, J2 | 2 | Conn_01x04_Female | Conn_01x04_Female-Connector | Keebio-Parts:TRRS-PJ-320A |  |  |  | 
| SW1, SW2, SW3, SW4, SW5, SW6, SW7, SW8, SW9, SW10, SW11, SW12, SW13, SW14, SW15, SW16, SW17, SW18, SW19, SW20, SW21, SW22, SW23, SW24, SW25, SW26, SW27, SW28, SW29, SW30, SW31, SW32, SW33, SW34, SW35, SW36, SW37, SW38, SW39, SW40, SW41, SW42 | 42 | SW_Push | SW_Push | MXMountLP:MXMountLP-1U | Push button switch, generic, two pins |  |  | 
| U1, U2 | 2 | ProMicro | ProMicro | promicro:ProMicro |  |  |  | 

## mounting_holes
| x | y | package | value | ref | size | 
| --- | --- | --- | --- | --- | --- | 
| 0.0 | 24.87 | MountingHole | HOLE | U4 | m3 | 
| 0.0 | 43.86 | MountingHole | HOLE | U4 | m3 | 
| 75.97 | 47.38 | MountingHole | HOLE | U4 | m3 | 
| 43.16 | 7.62 | MountingHole | HOLE | U4 | m3 | 
| 89.72 | 0.01 | MountingHole | HOLE | U4 | m3 | 
| 194.35 | 7.61 | MountingHole | HOLE | U4 | m3 | 
| 161.54 | 47.37 | MountingHole | HOLE | U4 | m3 | 
| 237.49 | 43.88 | MountingHole | HOLE | U4 | m3 | 
| 237.49 | 24.88 | MountingHole | HOLE | U4 | m3 | 
| 147.78 | 0.0 | MountingHole | HOLE | U4 | m3 |

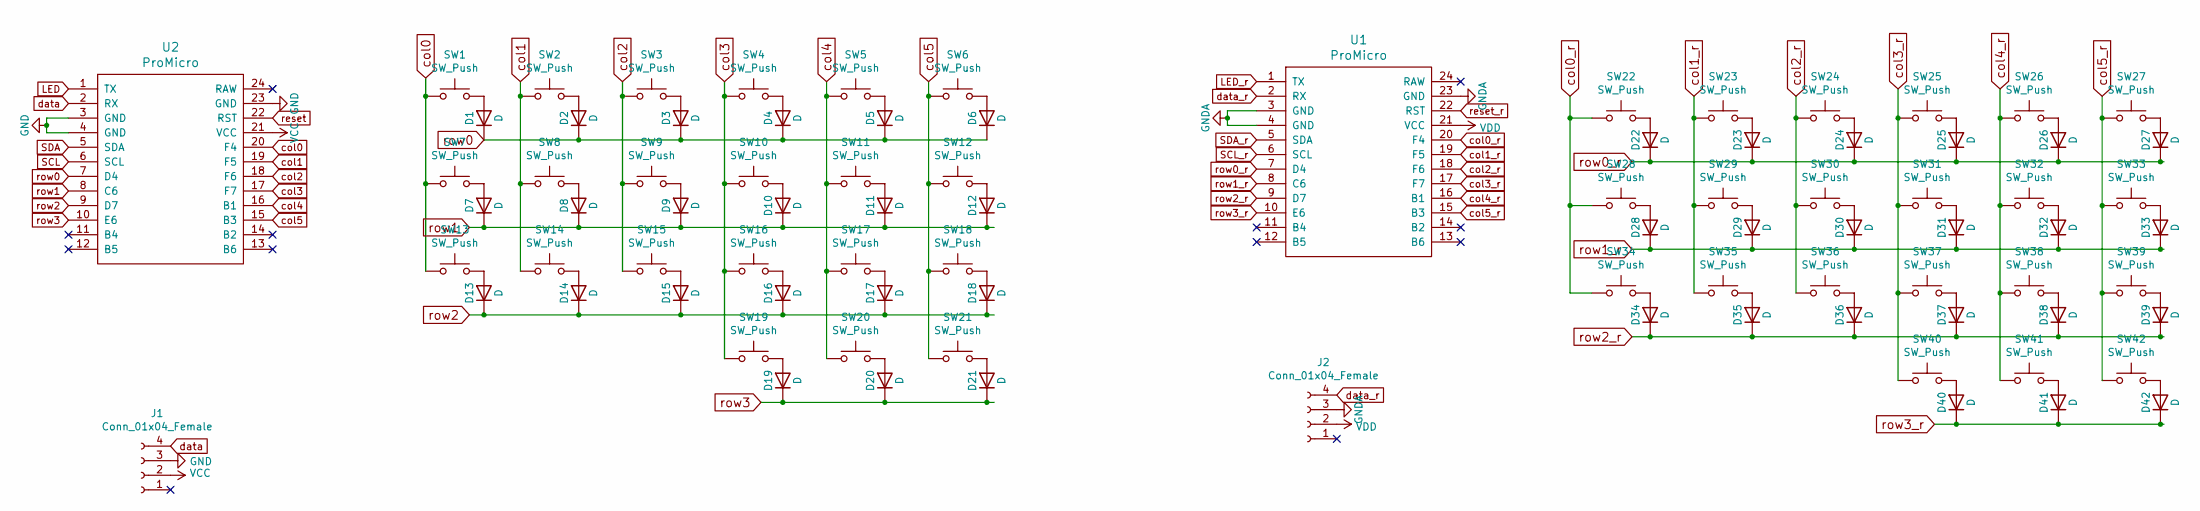
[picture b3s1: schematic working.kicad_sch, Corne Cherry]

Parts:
D1, D2, D3, D4, D5, D6, D7, D8, D9, D10, D11, D12, D13, D14, D15, D16, D17, D18, D19, D20, D21, D22, D23, D24, D25, D26, D27, D28, D29, D30, D31, D32, D33, D34, D35, D36, D37, D38, D39, D40, D41, D42: D; Diode-Hybrid-Back
J1, J2: Conn_01x04_Female; TRRS-PJ-320A
SW1, SW2, SW3, SW4, SW5, SW6, SW7, SW8, SW9, SW10, SW11, SW12, SW13, SW14, SW15, SW16, SW17, SW18, SW19, SW20, SW21, SW22, SW23, SW24, SW25, SW26, SW27, SW28, SW29, SW30, SW31, SW32, SW33, SW34, SW35, SW36, SW37, SW38, SW39, SW40, SW41, SW42: SW_Push; MXMountLP-1U
U1, U2: ProMicro

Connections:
GND: J1.3, U2.3 (GND), U2.4 (GND), U2.23 (GND)
GNDA: J2.3, U1.3 (GND), U1.4 (GND), U1.23 (GND)
LED: U2.1 (TX)
LED_r: U1.1 (TX)
unnamed: D1.2 (A), SW1.2
unnamed: D2.2 (A), SW2.2
unnamed: D3.2 (A), SW3.2
unnamed: D4.2 (A), SW4.2
unnamed: D5.2 (A), SW5.2
unnamed: D6.2 (A), SW6.2
unnamed: D7.2 (A), SW7.2
unnamed: D8.2 (A), SW8.2
unnamed: D9.2 (A), SW9.2
unnamed: D10.2 (A), SW10.2
unnamed: D11.2 (A), SW11.2
unnamed: D12.2 (A), SW12.2
unnamed: D13.2 (A), SW13.2
unnamed: D14.2 (A), SW14.2
unnamed: D15.2 (A), SW15.2
unnamed: D16.2 (A), SW16.2
unnamed: D17.2 (A), SW17.2
unnamed: D18.2 (A), SW18.2
unnamed: D19.2 (A), SW19.2
unnamed: D20.2 (A), SW20.2
unnamed: D21.2 (A), SW21.2
unnamed: D22.2 (A), SW22.2
unnamed: D23.2 (A), SW23.2
unnamed: D24.2 (A), SW24.2
unnamed: D25.2 (A), SW25.2
unnamed: D26.2 (A), SW26.2
unnamed: D27.2 (A), SW27.2
unnamed: D28.2 (A), SW28.2
unnamed: D29.2 (A), SW29.2
unnamed: D30.2 (A), SW30.2
unnamed: D31.2 (A), SW31.2
unnamed: D32.2 (A), SW32.2
unnamed: D33.2 (A), SW33.2
unnamed: D34.2 (A), SW34.2
unnamed: D35.2 (A), SW35.2
unnamed: D36.2 (A), SW36.2
unnamed: D37.2 (A), SW37.2
unnamed: D38.2 (A), SW38.2
unnamed: D39.2 (A), SW39.2
unnamed: D40.2 (A), SW40.2
unnamed: D41.2 (A), SW41.2
unnamed: D42.2 (A), SW42.2
SCL: U2.6 (SCL)
SCL_r: U1.6 (SCL)
SDA: U2.5 (SDA)
SDA_r: U1.5 (SDA)
VCC: J1.2, U2.21 (VCC)
VDD: J2.2, U1.21 (VCC)
col0: SW1.1, SW7.1, SW13.1, U2.20 (F4)
col0_r: SW22.1, SW28.1, SW34.1, U1.20 (F4)
col1: SW2.1, SW8.1, SW14.1, U2.19 (F5)
col1_r: SW23.1, SW29.1, SW35.1, U1.19 (F5)
col2: SW3.1, SW9.1, SW15.1, U2.18 (F6)
col2_r: SW24.1, SW30.1, SW36.1, U1.18 (F6)
col3: SW4.1, SW10.1, SW16.1, SW19.1, U2.17 (F7)
col3_r: SW25.1, SW31.1, SW37.1, SW40.1, U1.17 (F7)
col4: SW5.1, SW11.1, SW17.1, SW20.1, U2.16 (B1)
col4_r: SW26.1, SW32.1, SW38.1, SW41.1, U1.16 (B1)
col5: SW6.1, SW12.1, SW18.1, SW21.1, U2.15 (B3)
col5_r: SW27.1, SW33.1, SW39.1, SW42.1, U1.15 (B3)
data: J1.4, U2.2 (RX)
data_r: J2.4, U1.2 (RX)
reset: U2.22 (RST)
reset_r: U1.22 (RST)
row0: D1.1 (K), D2.1 (K), D3.1 (K), D4.1 (K), D5.1 (K), D6.1 (K), U2.7 (D4)
row0_r: D22.1 (K), D23.1 (K), D24.1 (K), D25.1 (K), D26.1 (K), D27.1 (K), U1.7 (D4)
row1: D7.1 (K), D8.1 (K), D9.1 (K), D10.1 (K), D11.1 (K), D12.1 (K), U2.8 (C6)
row1_r: D28.1 (K), D29.1 (K), D30.1 (K), D31.1 (K), D32.1 (K), D33.1 (K), U1.8 (C6)
row2: D13.1 (K), D14.1 (K), D15.1 (K), D16.1 (K), D17.1 (K), D18.1 (K), U2.9 (D7)
row2_r: D34.1 (K), D35.1 (K), D36.1 (K), D37.1 (K), D38.1 (K), D39.1 (K), U1.9 (D7)
row3: D19.1 (K), D20.1 (K), D21.1 (K), U2.10 (E6)
row3_r: D40.1 (K), D41.1 (K), D42.1 (K), U1.10 (E6)

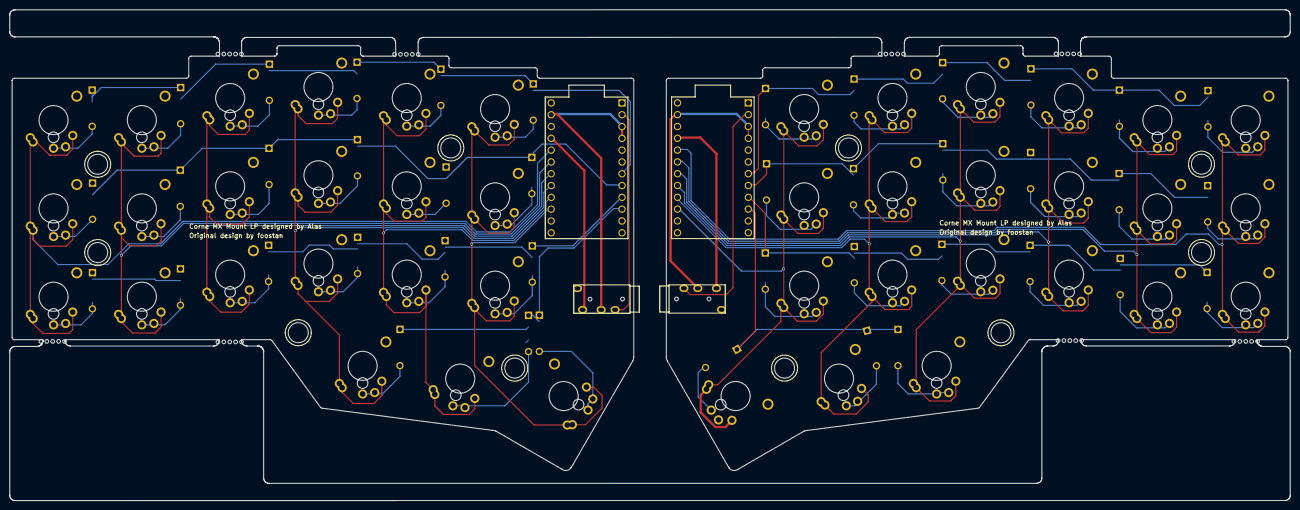
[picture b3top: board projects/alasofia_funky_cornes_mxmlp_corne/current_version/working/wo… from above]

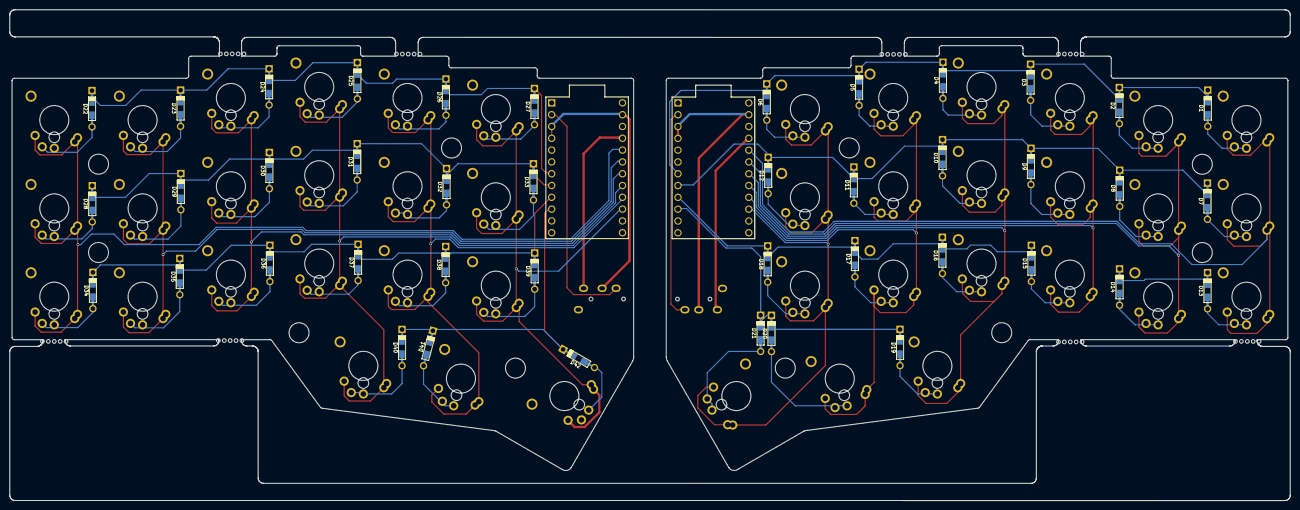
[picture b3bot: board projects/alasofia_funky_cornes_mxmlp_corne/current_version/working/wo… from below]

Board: 2 copper layers, 275.5 x 105.6 mm, 98 parts (2 on the bottom side), 68 nets.

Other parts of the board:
U4, U4#2, U4#3, U4#4, U4#5, U4#6, U4#7, U4#8, U4#9, U4#10: HOLE; MountingHole

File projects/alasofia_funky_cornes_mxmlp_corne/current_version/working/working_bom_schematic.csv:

"Source:","C:\gh\oomlout_oomp_project_bot_v_2\projects\alasofia_funky_cornes_mxmlp_corne\current_version\working\working.kicad_sch"
"Date:","18/09/2023 19:16:30"
"Tool:","Eeschema 7.0.6"
"Generator:","C:/Program Files/KiCad/7.0/bin/scripting/plugins/bom_csv_grouped_by_value_with_fp.py"
"Component Count:","88"
"Ref","Qnty","Value","Cmp name","Footprint","Description","Vendor","DNP"
"D1, D2, D3, D4, D5, D6, D7, D8, D9, D10, D11, D12, D13, D14, D15, D16, D17, D18, D19, D20, D21, D22, D23, D24, D25, D26, D27, D28, D29, D30, D31, D32, D33, D34, D35, D36, D37, D38, D39, D40, D41, D42","42","D","D","Keebio-Parts:Diode-Hybrid-Back","Diode","",""
"J1, J2","2","Conn_01x04_Female","Conn_01x04_Female-Connector","Keebio-Parts:TRRS-PJ-320A","","",""
"SW1, SW2, SW3, SW4, SW5, SW6, SW7, SW8, SW9, SW10, SW11, SW12, SW13, SW14, SW15, SW16, SW17, SW18, SW19, SW20, SW21, SW22, SW23, SW24, SW25, SW26, SW27, SW28, SW29, SW30, SW31, SW32, SW33, SW34, SW35, SW36, SW37, SW38, SW39, SW40, SW41, SW42","42","SW_Push","SW_Push","MXMountLP:MXMountLP-1U","Push button switch, generic, two pins","",""
"U1, U2","2","ProMicro","ProMicro","promicro:ProMicro","","",""
